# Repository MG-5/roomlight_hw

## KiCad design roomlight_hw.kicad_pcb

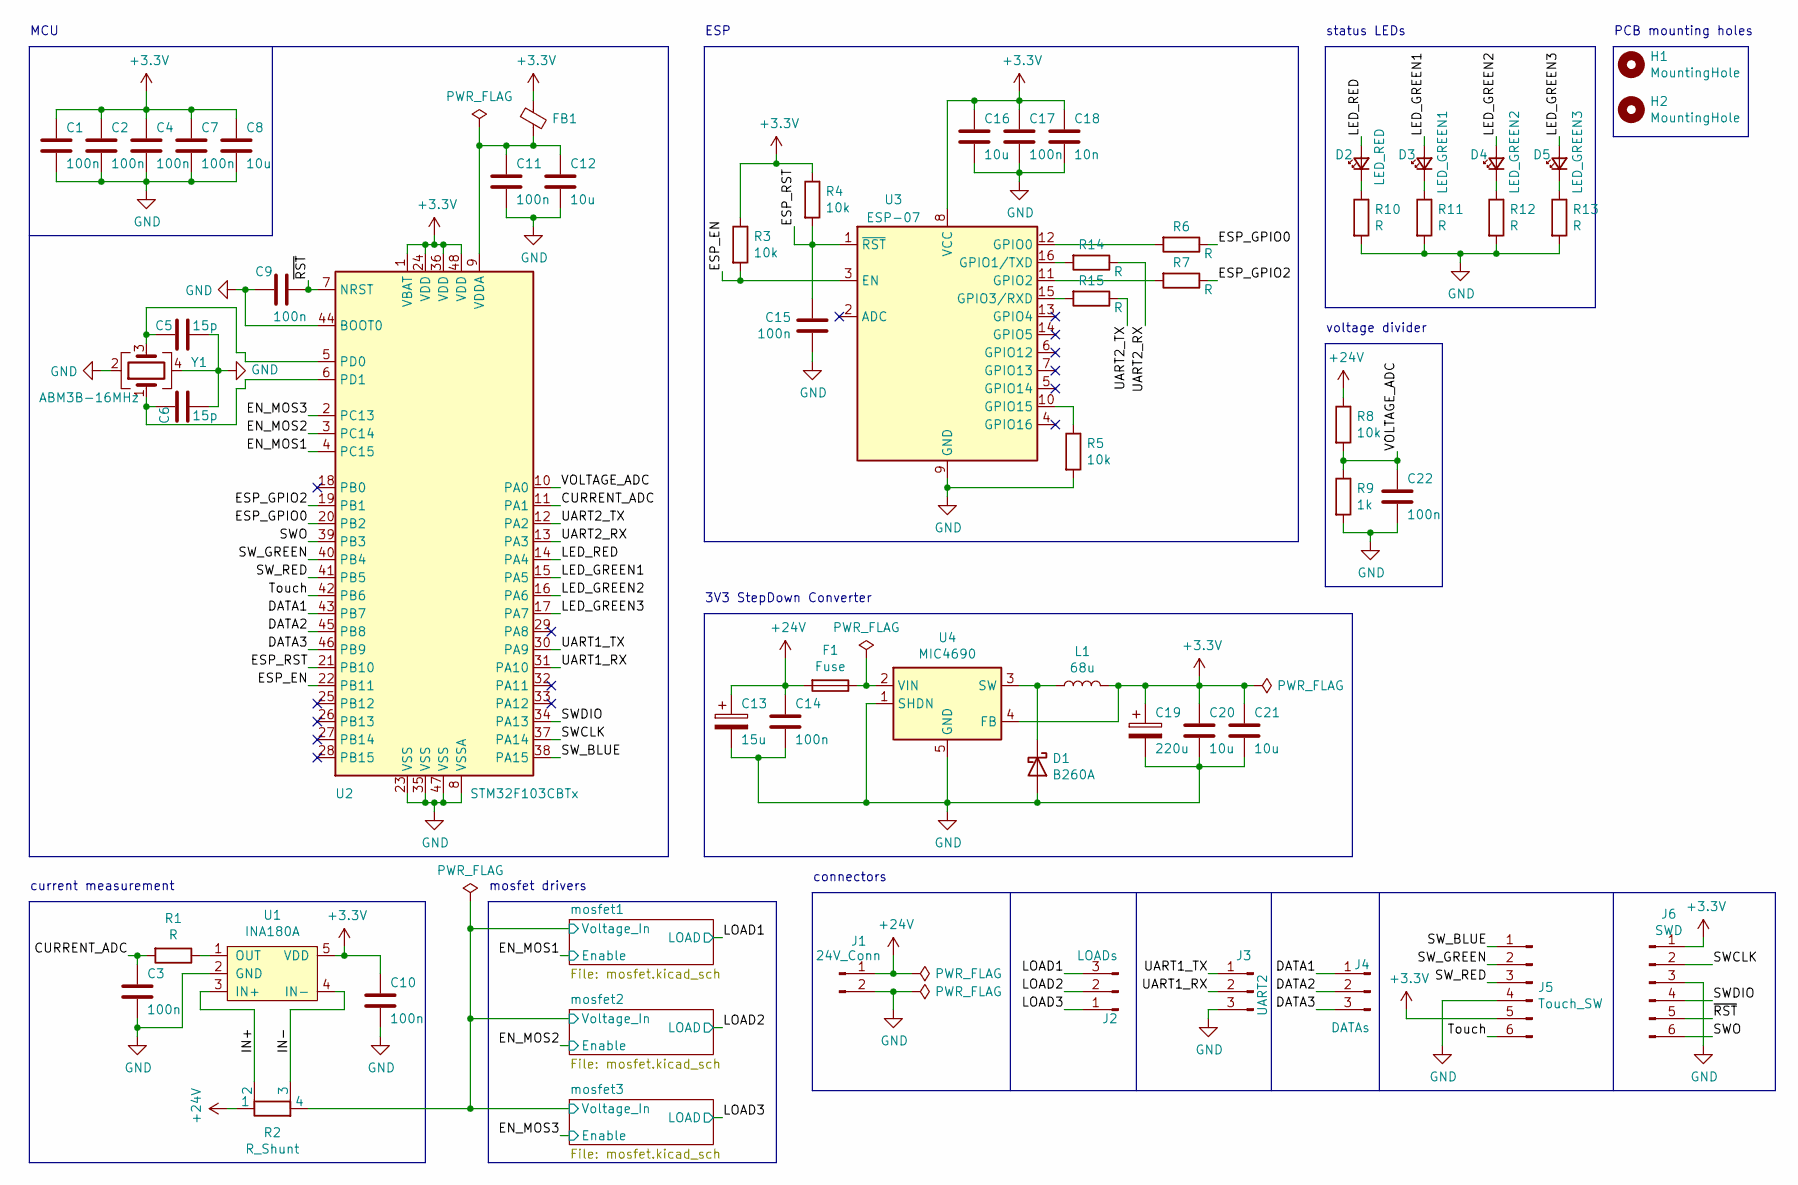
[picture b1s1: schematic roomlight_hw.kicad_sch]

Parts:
C1, C2, C3, C4, C7, C9, C10, C11, C14, C15, C17, C22: 100n; C_0603_1608Metric_Pad1.05x0.95mm_HandSolder
C5, C6: 15p; C_0402_1005Metric
C8, C12, C16, C20, C21: 10u; C_0805_2012Metric_Pad1.15x1.40mm_HandSolder
C13: 15u; CP_Radial_D5.0mm_P2.50mm
C18: 10n; C_0603_1608Metric_Pad1.05x0.95mm_HandSolder
C19: 220u; CP_Radial_D6.3mm_P2.50mm
D1: B260A; D_SMB
D2: LED_RED; LED_0805_2012Metric_Pad1.15x1.40mm_HandSolder
D3: LED_GREEN1; LED_0805_2012Metric_Pad1.15x1.40mm_HandSolder
D4: LED_GREEN2; LED_0805_2012Metric_Pad1.15x1.40mm_HandSolder
D5: LED_GREEN3; LED_0805_2012Metric_Pad1.15x1.40mm_HandSolder
F1: Fuse; Fuse_0603_1608Metric_Pad1.05x0.95mm_HandSolder
FB1: Ferrite_Bead_Small; L_0805_2012Metric_Pad1.15x1.40mm_HandSolder
H1, H2: MountingHole; MountingHole_3.2mm_M3_ISO14580
J1: 24V_Conn; DG306-5.0-02
J2: LOADs; DG306-5.0-03
J3: UART2; Molex_PicoBlade_53047-0310_1x03_P1.25mm_Vertical
J4: DATAs; Molex_PicoBlade_53047-0310_1x03_P1.25mm_Vertical
J5: Touch_SW; Molex_PicoBlade_53047-0610_1x06_P1.25mm_Vertical
J6: SWD; PinHeader_1x06_P2.54mm_Vertical
L1: 68u; L_Taiyo-Yuden_NR-60xx
R1, R6, R7, R10, R11, R12, R13, R14, R15: R; R_0603_1608Metric_Pad1.05x0.95mm_HandSolder
R2: R_Shunt; R_2512_6332Metric_KelvinShunt
R3, R4, R5, R8: 10k; R_0603_1608Metric_Pad1.05x0.95mm_HandSolder
R9: 1k; R_0603_1608Metric_Pad1.05x0.95mm_HandSolder
U1: INA180A; SOT-23-5
U2: STM32F103CBTx; LQFP-48_7x7mm_P0.5mm
U3: ESP-07
U4: MIC4690; SOIC-8_3.9x4.9mm_P1.27mm
Y1: ABM3B-16MHz; Crystal_SMD_Abracon_ABM3B-4Pin_5.0x3.2mm

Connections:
+3.3V: C1.1, C2.1, C4.1, C7.1, C8.1, C10.2, C16.1, C17.1, C18.1, C19.1, C20.1, C21.1, FB1.1, J5.5, J6.1, L1.2, R3.1, R4.1, U1.5 (VDD), U2.1 (VBAT), U2.24 (VDD), U2.36 (VDD), U2.48 (VDD), U3.8 (VCC), U4.4 (FB)
+24V: C13.1, C14.1, F1.2, J1.1, R2.1, R8.1
/CURRENT_ADC: C3.2, R1.2, U2.11 (PA1)
/DATA1: J4.1, U2.43 (PB7)
/DATA2: J4.2, U2.45 (PB8)
/DATA3: J4.3, U2.46 (PB9)
/EN_MOS1: U2.4 (PC15); also elsewhere on the board
/EN_MOS2: U2.3 (PC14); also elsewhere on the board
/EN_MOS3: U2.2 (PC13); also elsewhere on the board
/ESP_EN: R3.2, U2.22 (PB11), U3.3 (EN)
/ESP_GPIO0: R6.1, U2.20 (PB2)
/ESP_GPIO2: R7.1, U2.19 (PB1)
/ESP_RST: C15.2, R4.2, U2.21 (PB10), U3.1 (~RST)
/IN+: R2.2, U1.3 (IN+)
/IN-: R2.3, U1.4 (IN-)
/LED_GREEN1: D3.2 (A), U2.15 (PA5)
/LED_GREEN2: D4.2 (A), U2.16 (PA6)
/LED_GREEN3: D5.2 (A), U2.17 (PA7)
/LED_RED: D2.2 (A), U2.14 (PA4)
/LOAD1: J2.3; also elsewhere on the board
/LOAD2: J2.2; also elsewhere on the board
/LOAD3: J2.1; also elsewhere on the board
/SWCLK: J6.2, U2.37 (PA14)
/SWDIO: J6.4, U2.34 (PA13)
/SWO: J6.6, U2.39 (PB3)
/SW_BLUE: J5.1, U2.38 (PA15)
/SW_GREEN: J5.2, U2.40 (PB4)
/SW_RED: J5.3, U2.41 (PB5)
/Touch: J5.6, U2.42 (PB6)
/UART1_RX: J3.2, U2.31 (PA10)
/UART1_TX: J3.1, U2.30 (PA9)
/UART2_RX: R14.1, U2.13 (PA3)
/UART2_TX: R15.1, U2.12 (PA2)
/VOLTAGE_ADC: C22.1, R8.2, R9.1, U2.10 (PA0)
/mosfet1/Voltage_In: R2.4; also elsewhere on the board
/~RST: C9.1, J6.5, U2.7 (NRST)
GND: C1.2, C2.2, C3.1, C4.2, C5.2, C6.2, C7.2, C8.2, C9.2, C10.1, C11.2, C12.2, C13.2, C14.2, C15.1, C16.2, C17.2, C18.2, C19.2, C20.2, C21.2, C22.2, D1.2 (A), J1.2, J3.3, J5.4, J6.3, R5.2, R9.2, R10.2, R11.2, R12.2, R13.2, U1.2 (GND), U2.8 (VSSA), U2.23 (VSS), U2.35 (VSS), U2.44 (BOOT0), U2.47 (VSS), U3.9 (GND), U4.1 (SHDN), U4.5 (GND), U4.6 (GND), U4.7 (GND), U4.8 (GND), Y1.2, Y1.4; also elsewhere on the board
unnamed: C5.1, U2.5 (PD0), Y1.3
unnamed: C6.1, U2.6 (PD1), Y1.1
unnamed: C11.1, C12.1, FB1.2, U2.9 (VDDA)
unnamed: D1.1 (K), L1.1, U4.3 (SW)
unnamed: D2.1 (K), R10.1
unnamed: D3.1 (K), R11.1
unnamed: D4.1 (K), R12.1
unnamed: D5.1 (K), R13.1
unnamed: F1.1, U4.2 (VIN)
unnamed: R1.1, U1.1 (OUT)
unnamed: R5.1, U3.10 (GPIO15)
unnamed: R6.2, U3.12 (GPIO0)
unnamed: R7.2, U3.11 (GPIO2)
unnamed: R14.2, U3.16 (GPIO1/TXD)
unnamed: R15.2, U3.15 (GPIO3/RXD)

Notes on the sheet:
mosfet drivers
ESP
PCB mounting holes
3V3 StepDown Converter
status LEDs
current measurement
connectors
voltage divider
MCU

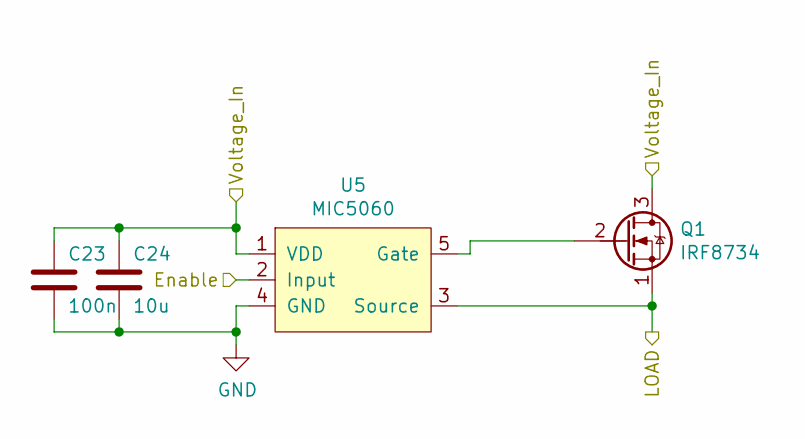
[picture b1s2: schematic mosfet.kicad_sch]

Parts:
C23: 100n; C_0603_1608Metric_Pad1.05x0.95mm_HandSolder
C24: 10u; C_0805_2012Metric_Pad1.15x1.40mm_HandSolder
Q1: IRF8734; SOIC-8-MOSFET
U5: MIC5060; MLF-8-1EP_3x3mm_P0.65mm_EP1.55x2.3mm

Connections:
/EN_MOS1: U5.2 (Input); also elsewhere on the board
/LOAD1: Q1.1 (S), U5.3 (Source); also elsewhere on the board
/mosfet1/Voltage_In: C23.1, C24.1, Q1.3 (D), U5.1 (VDD); also elsewhere on the board
GND: C23.2, C24.2, U5.4 (GND); also elsewhere on the board
unnamed: Q1.2 (G), U5.5 (Gate)

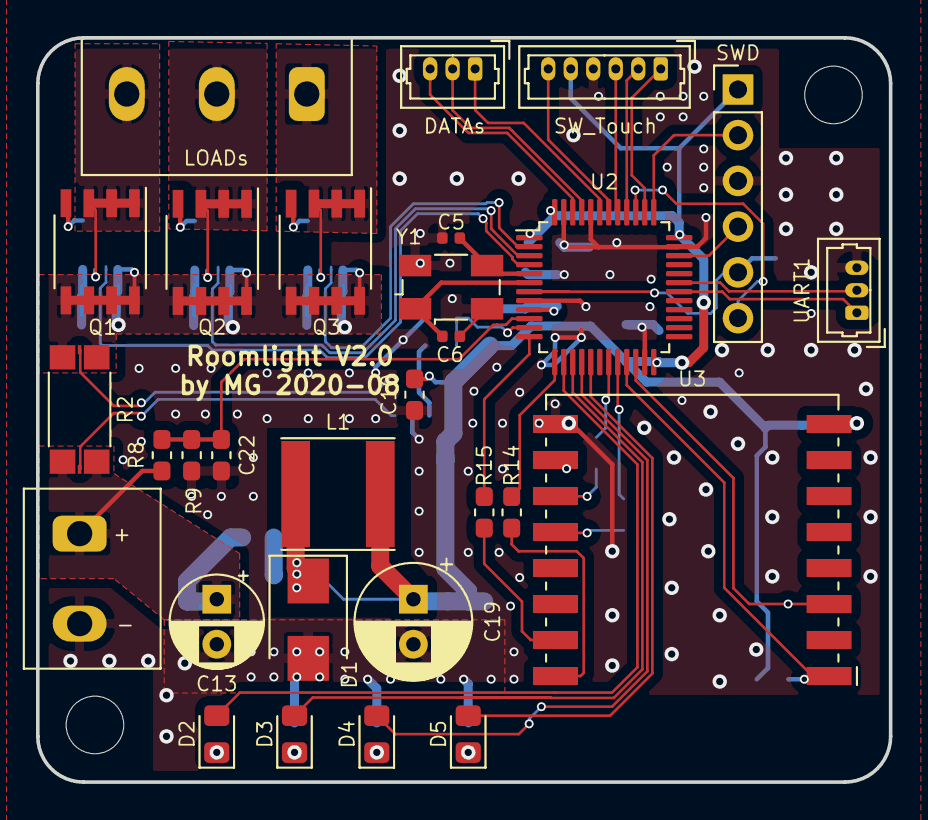
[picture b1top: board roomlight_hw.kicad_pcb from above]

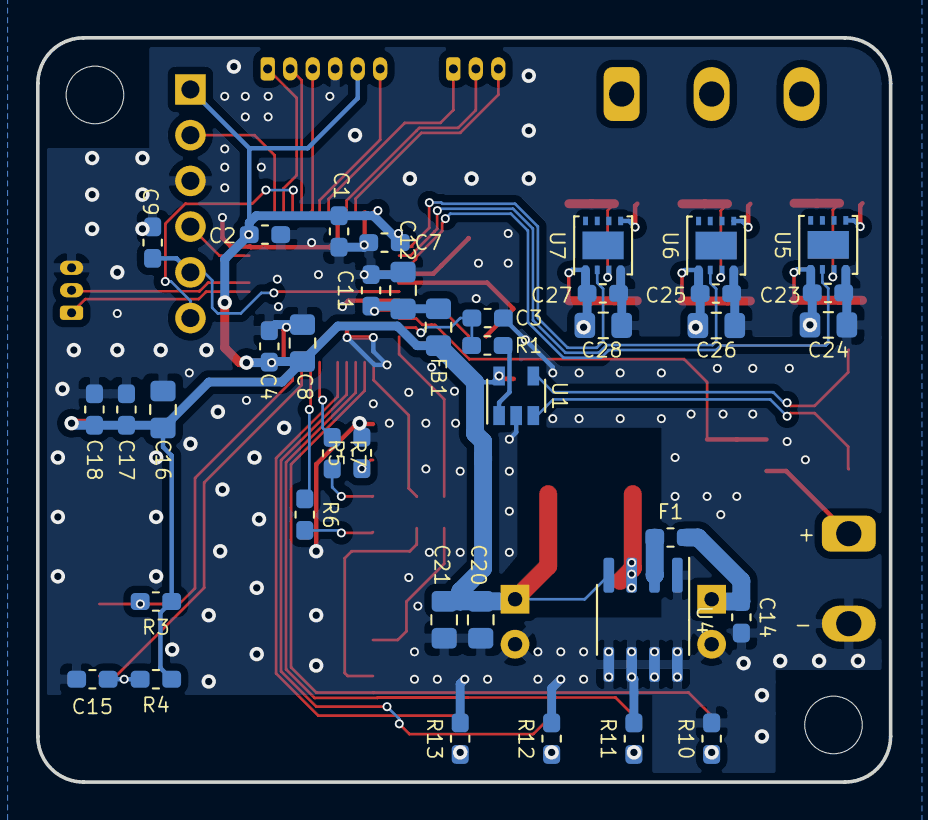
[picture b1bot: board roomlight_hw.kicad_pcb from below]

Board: 2 copper layers, 47.4 x 41.3 mm, 70 parts (39 on the bottom side), 55 nets.

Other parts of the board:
C25, C27: 100n; C_0603_1608Metric_Pad1.05x0.95mm_HandSolder
C26, C28: 10u; C_0805_2012Metric_Pad1.15x1.40mm_HandSolder
Q2, Q3: IRF8734; SOIC-8-MOSFET
U6, U7: MIC5060; MLF-8-1EP_3x3mm_P0.65mm_EP1.55x2.3mm

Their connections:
/EN_MOS2: U6.2 (Input); also elsewhere on the board
/EN_MOS3: U7.2 (Input); also elsewhere on the board
/LOAD2: Q2.1 (S), U6.3 (Source); also elsewhere on the board
/LOAD3: Q3.1 (S), U7.3 (Source); also elsewhere on the board
/mosfet1/Voltage_In: C25.1, C26.1, C27.1, C28.1, Q2.3 (D), Q3.3 (D), U6.1 (VDD), U7.1 (VDD); also elsewhere on the board
GND: C25.2, C26.2, C27.2, C28.2, U6.4 (GND), U7.4 (GND); also elsewhere on the board
unnamed: Q2.2 (G), U6.5 (Gate)
unnamed: Q3.2 (G), U7.5 (Gate)

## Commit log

2020-07-23 Init
2020-07-25 Finish schematic
2020-07-25 Assign footprints
2020-07-25 Fix wrong footprint
2020-07-26 Finish PCB
2020-08-15 Remove unneeded file
2020-08-17 Improve UART connection and a lot of ground planes
2022-09-29 Create LICENSE
2022-11-07 Update to KiCad 6
2022-11-07 Migrate symbol library to new format
2022-11-07 Update paths to 3D models
